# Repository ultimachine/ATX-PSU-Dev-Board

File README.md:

##About
This is an ATX breakout board inspired and based on <http://www.sparkfun.com/products/9558>.

##Purchasing
The board can be purchased from UltiMachine.com in PCB-only, DIY-kit, or assembled form at <https://ultimachine.com/content/atx-psu-dev-board>.

##License
This work is licensed under the [Creative Commons Attribution-ShareAlike 3.0 United States License](http://creativecommons.org/licenses/by-sa/3.0/us/).

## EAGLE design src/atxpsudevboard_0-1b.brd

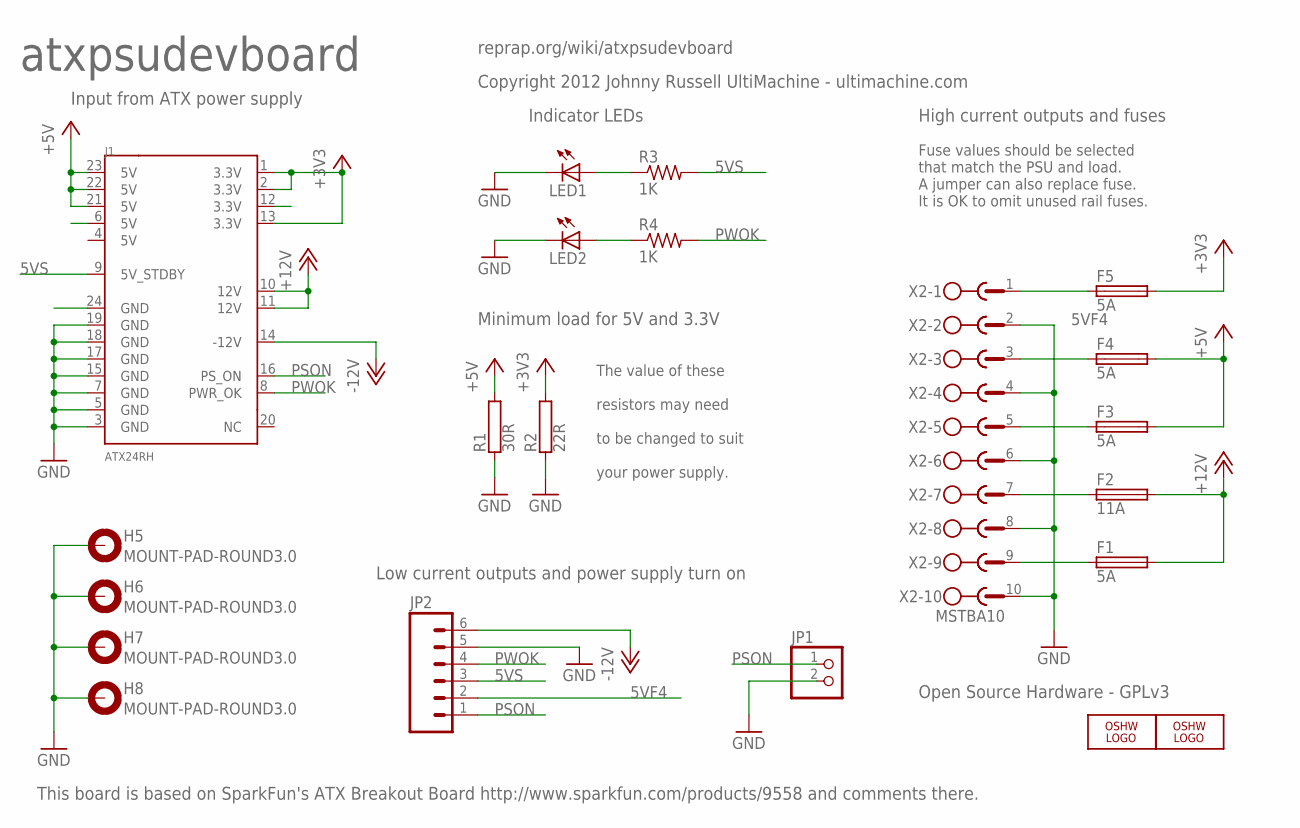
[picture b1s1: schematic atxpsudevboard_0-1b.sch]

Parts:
F1, F3, F4, F5: 5A; MFR1100
F2: 11A; MFR1100
H5, H6, H7, H8: MOUNT-PAD-ROUND3.0; 3,0-PAD
J1: ATX24RH; ATX24_RIGHT_ANGLE
JP1: PINHD-1X2; 1X02
JP2: M06LONGPADS; 1X06_LONGPADS
LED1, LED2: LED3MM
LOGO1: OSHW_LOGO_FILLX0100-NT; OSHW_FILLX100_NOTEXT
LOGO2: OSHW_LOGO_FILLX0200-NT; OSHW_FILLX200_NOTEXT
R1: 30R; HPS923
R2: 22R; CA4050
R3, R4: 1K; 0207/7
X2: MSTBA10

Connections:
5VF4: F4.1, JP2.2, X2.3
5VS: J1.9 (5V_STDBY), JP2.3, R3.2
+3V3: F5.2, J1.1 (3.3V), J1.2 (3.3V), J1.13 (3.3V), R2.2
+5V: F3.2, F4.2, J1.21 (5V), J1.22 (5V), J1.23 (5V), R1.2
+12V: F1.2, F2.2, J1.10 (12V), J1.11 (12V)
-12V: J1.14 (-12V), JP2.6
GND: H5.B3,0, H6.B3,0, H7.B3,0, H8.B3,0, J1.3 (GND), J1.5 (GND), J1.7 (GND), J1.15 (GND), J1.17 (GND), J1.18 (GND), J1.19 (GND), JP1.2, JP2.5, LED1.K (C), LED2.K (C), R1.1, R2.1, X2.2, X2.4, X2.6, X2.8, X2.10
unnamed: F2.1, X2.7
unnamed: F1.1, X2.9
unnamed: F3.1, X2.5
unnamed: F5.1, X2.1
unnamed: LED1.A, R3.1
unnamed: LED2.A, R4.1
PSON: J1.16 (PS_ON), JP1.1, JP2.1
PWOK: J1.8 (PWR_OK), JP2.4, R4.2

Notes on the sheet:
atxpsudevboard
Input from ATX power supply
Indicator LEDs
Minimum load for 5V and 3.3V
to be changed to suit
your power supply.
The value of these
resistors may need
Low current outputs and power supply turn on
High current outputs and fuses
Copyright 2012 Johnny Russell UltiMachine - ultimachine.com
reprap.org/wiki/atxpsudevboard
Open Source Hardware - GPLv3
This board is based on SparkFun's ATX Breakout Board http://www.sparkfun.com/products/9558 and comments there.
Fuse values should be selected
that match the PSU and load.
A jumper can also replace fuse.
It is OK to omit unused rail fuses.

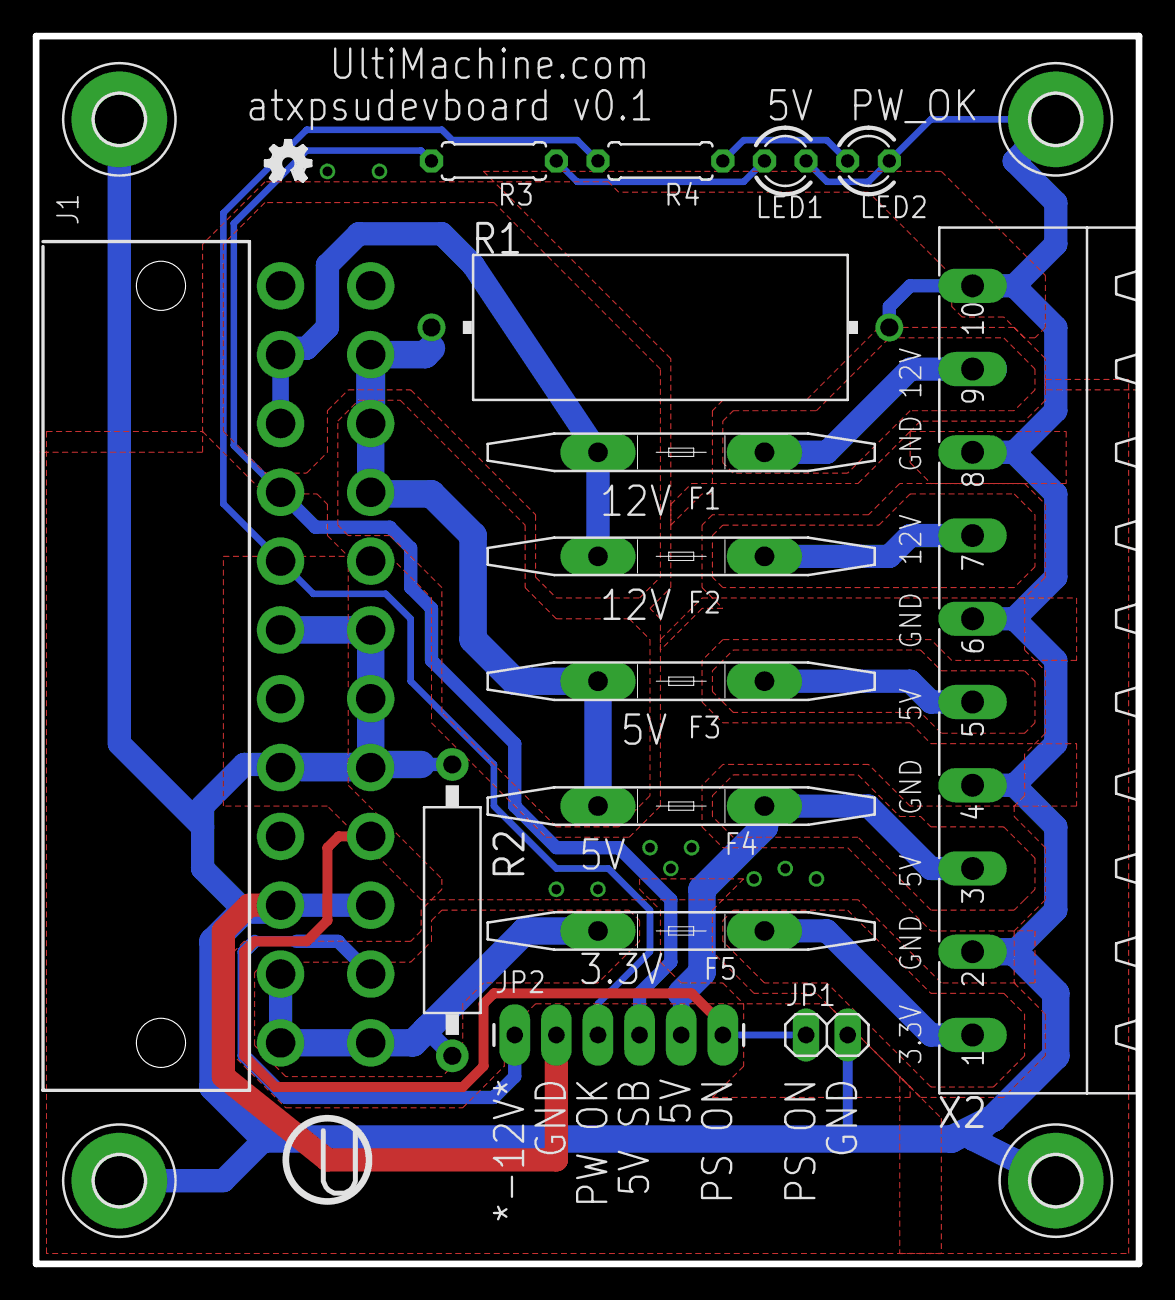
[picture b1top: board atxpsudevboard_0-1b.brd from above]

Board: 2 copper layers, 67.3 x 74.9 mm, 21 parts (0 on the bottom side), 15 nets.

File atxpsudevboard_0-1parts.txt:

Partlist

Exported from atxpsudevboard_0-1.sch at 1/9/2012 9:30:20 AM

EAGLE Version 6.0.0 Copyright (c) 1988-2011 CadSoft

Assembly variant: 

Part     Value /Newark No.  Device             Package           Library         Sheet

F1       5A   16F1791       PTCFUSEMFR1100     MFR1100           RepRapjr        1
F2       11A  60H8377       PTCFUSEMFR1100     MFR1100           RepRapjr        1
F3       5A   16F1791       PTCFUSEMFR1100     MFR1100           RepRapjr        1
F4       5A   16F1791       PTCFUSEMFR1100     MFR1100           RepRapjr        1
F5       5A   16F1791       PTCFUSEMFR1100     MFR1100           RepRapjr        1
H5       MOUNT-PAD-ROUND3.0 MOUNT-PAD-ROUND3.0 3,0-PAD           holes           1
H6       MOUNT-PAD-ROUND3.0 MOUNT-PAD-ROUND3.0 3,0-PAD           holes           1
H7       MOUNT-PAD-ROUND3.0 MOUNT-PAD-ROUND3.0 3,0-PAD           holes           1
H8       MOUNT-PAD-ROUND3.0 MOUNT-PAD-ROUND3.0 3,0-PAD           holes           1
J1       ATX24RH            ATX24RH            ATX24_RIGHT_ANGLE SparkFun        1
JP1                         PINHD-1X2          1X02              pinhead         1
JP2                         M06LONGPADS        1X06_LONGPADS     SparkFun        1
LED1                        LED3MM             LED3MM            led             1
LED2                        LED3MM             LED3MM            led             1
R1       30R (5W) 16R2247   RHPS923            HPS923            resistor-power  1
R2       22R (3W) 74M3349   RCA4050            CA4050            resistor-power  1
R3       1K                 R-US_0207/7        0207/7            resistor        1
R4       1K                 R-US_0207/7        0207/7            resistor        1
X2       MSTBA10            MSTBA10            MSTBA10           con-phoenix-508 1
         MSTBA pluggables for each

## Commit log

2013-01-31 some progress on a double-documenting workflow
2013-01-31 rename files and remove step 2
2013-02-02 new workflow and commiting because I didnt use git m
2013-02-02 clean png dir
2013-02-02 change steps
2013-05-07 reworked with build script
2013-05-13 little hack to make the PDF look ok
2013-05-13 move all the outputs into folders
2013-05-13 update script and title page for new locations
2013-05-16 update generation notes
2013-05-16 rebuild
2013-05-16 minor corections
2013-05-16 rework the LaTeX layout and add more content and clarifications
2013-05-16 md syntax correction
2013-05-16 modification for RepRap.org mediawiki
2013-05-23 populate License.md and fix grammar
